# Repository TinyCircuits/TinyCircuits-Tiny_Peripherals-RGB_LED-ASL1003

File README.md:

# TinyCircuits-Tiny_Peripherals-RGB_LED-ASL1003
# ASL1003 Rev1

The design files are located under design_files/ for the TinyCircuits ASL1003 Rev 1 PCB.  This is a Tiny peripheral board that has an 1206 LED and resistor, along with pads to solder to.

Format is in Cadsoft Eagle format - Eagle version 6.2 was used for the original design.

For more infomation on this, check out the product page at TinyCircuits.com: https://tinycircuits.com/collections/tinylily/products/tinylily-rgb-led

# License:

Design by TinyCircuits.
All design files are released under the Creative Commons Attribution Share-Alike 3.0 License, see the following link for details: http://creativecommons.org/licenses/by-sa/3.0

All text above must be included in any redistribution or derived design

This project uses designs and concepts developed as part of the Arduino project and the LilyPad project.  The TinyCircuits design files themselves (schematics, PCB and libraries) are not directly derived from these works' design files and have been created new, however the concepts and basic architecture behind the TinyDuino and TinyLily products are derived and we thank the hard work of the organizations below for their contributions to open-source hardware:
  
Original Arduino Uno Design by Team Arduino

LilyPad Arduino Design by Leah Buechley and Sparkfun Electronics

Please support the open-source hardware community

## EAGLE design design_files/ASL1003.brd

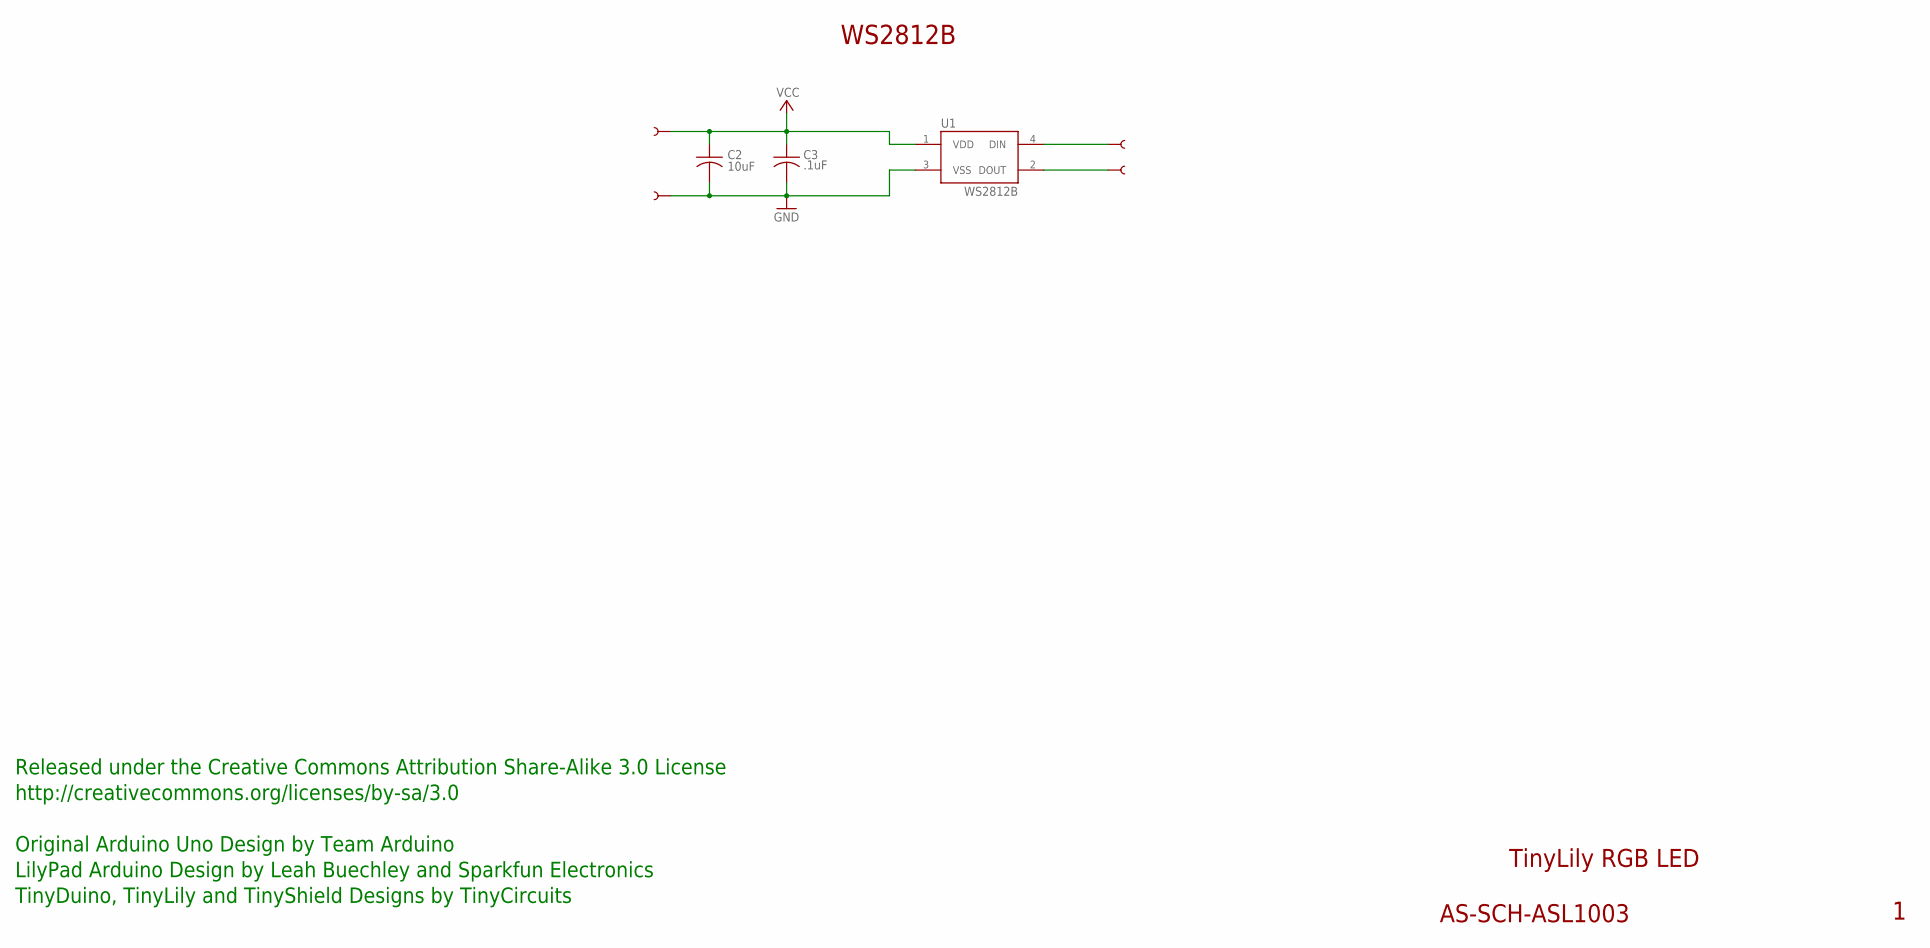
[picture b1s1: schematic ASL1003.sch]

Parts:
C2: 10uF; C0603; PARTNO AS-ITM-00002
C3: .1uF; C0402; PARTNO AS-ITM-00008
U1: WS2812B
U$3, U$7, U$8, U$9: SEWTABTH_10MM; SEWTAP_TH_10MM

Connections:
GND: C2.2, C3.2, U1.3 (VSS), U$7.1
unnamed: U1.4 (DIN), U$3.1
unnamed: U1.2 (DOUT), U$9.1
VCC: C2.1, C3.1, U1.1 (VDD), U$8.1

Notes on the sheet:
WS2812B
TinyLily RGB LED
AS-SCH-ASL1003
Released under the Creative Commons Attribution Share-Alike 3.0 License
http://creativecommons.org/licenses/by-sa/3.0
Original Arduino Uno Design by Team Arduino
TinyDuino, TinyLily and TinyShield Designs by TinyCircuits
LilyPad Arduino Design by Leah Buechley and Sparkfun Electronics

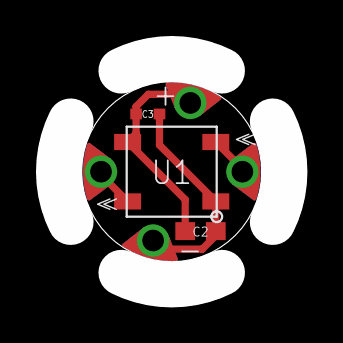
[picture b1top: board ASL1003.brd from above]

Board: 2 copper layers, 10.0 x 10.0 mm, 8 parts (0 on the bottom side), 4 nets.

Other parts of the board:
U$6: DOCFIELD-TINYCIRCUITS-PCB

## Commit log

2019-01-04 update format
2019-05-31 added examples and images
2019-05-31 added .zip files
2019-06-03 added animation
2019-06-06 image
2019-06-26 added materials image
2020-02-13 new pic
2020-08-28 Add CAD data
